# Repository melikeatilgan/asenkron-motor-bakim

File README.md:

# Asenkron motor: arıza analizi, bakım planı ve izleme kartları

15 kW'lık bir pompa motorunun hangi yollardan arızalanabileceğini arıza
ağaçlarıyla çıkardım. Buna göre aylık bakım formunu ve arıza anında kullanılacak
bir cep kartını hazırladım. Analiz, titreşimin ve yatak sıcaklığının iki aylık
kontrol arasında hiç izlenmediğini gösterdi. Bu boşluğu kapatmak için KiCad'de
üç kart tasarladım.

## Proje kısaca

**1. Arıza analizi** ([01-analiz/](01-analiz/)). Motorda ters gidebilecek üç
şeyi ele aldım: aşırı ısınma, aşırı titreşim, aşırı akım. Her birini kök
nedenlerine kadar bir arıza ağacıyla açtım. Python betiği hangi nedenlerin
birlikte arızaya yol açtığını hesaplıyor; aşağıdaki 144 / 21 / 18 sayıları
oradan geliyor. Analizin vardığı sonuç: titreşimi ve yatak sıcaklığını izleyen
otomatik bir koruma yok, bu arızalar ancak ayda bir yapılan kontrolde fark
ediliyor.

**2. Saha dokümanları** ([02-saha-dokumanlari/](02-saha-dokumanlari/)).

- **Aylık bakım formu** (A4, 2 sayfa): teknisyenin her ay doldurduğu 47
  maddelik kontrol listesi. Her madde arıza ağacındaki bir nedene bağlı.
- **Saha kartı** (A6 cep kartı): motor arıza verdiğinde ilk 5 dakikada ne
  yapılacağını anlatıyor. Ön yüzde "ısınıyor / titriyor / akım yüksek"
  adımları ve güvenlik kilitlemesi, arka yüzde bakılacak sınır değerlerin
  tablosu var.

**3. İzleme kartları** ([03-donanim/](03-donanim/)). Aylık kontrolün göremediği
aradaki zamanı bunlar kapatıyor:

- **Sensör başlığı:** motorun gövdesine vidalanıyor. Titreşimi ve iki yatağın
  sıcaklığını (PT100) sürekli ölçüyor, kabloyla ana karta gönderiyor.
- **Ana kart:** elektrik panosunun içinde duruyor. Üç faz akımını ve motor
  sargısındaki PTC sıcaklık sensörünü okuyor, ekran ve LED'lerle durumu
  gösteriyor. Sınır aşılırsa röle kontağını açıp motoru durduruyor. Asıl koruma
  değil; termik rölenin yanında ikinci bir güvenlik katmanı.
- **Telemetri geçidi:** pano dışında, Wi-Fi'li (ESP32). Ölçümleri ana karttan
  okuyup ağa (bilgisayar, telefon) aktarıyor. Yalnızca okuyor; üzerinde motoru
  durduracak bir çıkış yok.

Referans motor: WEG W22 IE3, 15 kW, 4 kutup, 400 V Δ, 160L gövde (ürün kodu
12863072). Değerler üreticinin veri föyünden alındı.

## İzleme kartları

```mermaid
flowchart LR
    MOT(["Motor"])
    SB["Sensör başlığı<br>motorun üstünde"]
    AK["Ana kart<br>pano içinde"]
    KON["Kontaktörün<br>kumanda devresi"]
    TG["Telemetri geçidi<br>pano dışında"]
    AG(["Ağ / SCADA"])
    MOT -- "titreşim, 2 yatak sıcaklığı" --> SB
    MOT -- "3 faz akımı, PTC" --> AK
    SB -- "izole RS-485" --> AK
    AK -- "röle kontağı" --> KON
    AK -- "izole RS-485, Modbus" --> TG
    TG -- "Wi-Fi" --> AG
```

<table>
  <tr>
    <td width="33%" align="center" valign="top">
      
      <br><b>Ana kart</b><br>
      Pano içinde. Faz akımlarını ve PTC'yi ölçer, LCD'de gösterir, sınır aşılırsa motoru durdurur.
      <br>STM32G474 · 190 × 145 mm
    </td>
    <td width="33%" align="center" valign="top">
      
      <br><b>Sensör başlığı</b><br>
      Motorun yatak gövdesine vidalanır. Titreşimi ve iki yatağın sıcaklığını ölçer.
      <br>STM32G071 · 90 × 72 mm
    </td>
    <td width="33%" align="center" valign="top">
      
      <br><b>Telemetri geçidi</b><br>
      Pano dışında. Ölçümleri ana karttan okuyup Wi-Fi ile ağa verir.
      <br>ESP32-S3 · 85 × 70 mm
    </td>
  </tr>
</table>

- **Şebeke gerilimi yalnızca röle kontağında.** O bölge kartın geri kalanından
  frezelenmiş bir yarıkla ayrıldı: 8 mm yüzeysel kaçak, 5,5 mm hava aralığı.
- **PTC girişi takviyeli izole** (ISOW7744). Devre kısa devre, normal, attı ve
  kopuk durumlarını ayırıyor; eşikleri en kötü durum hesabıyla seçtim.
- **Kartlar arası bağlantı izole RS-485.** Motor gövdesiyle pano arasındaki
  toprak farkı ölçüme karışmıyor.
- Üç kart da 4 katman. KiCad ERC ve DRC (şema-kart eşleşmesi dahil) 0.

Her kartın ayrıntısı, şeması ve üretim dosyaları: [03-donanim/](03-donanim/).
Kartlar ana koruma değil; sertifikalı termik röle ve PTC rölesine seri giren bir
erken uyarı katmanı.

## Arıza analizi

1. Üç tepe olay ölçülebilir biçimde tanımlandı: sargı sıcaklığının 155 °C'yi
   aşıp motorun kesilmemesi, yatak gövdesinde titreşimin 4,5 mm/s'yi aşması,
   rejimde akımın anma değerinin %110'unu geçmesi, kalkış akımının izin
   verilenden sık ya da uzun çekilmesi ya da ters akımla frenleme.
2. Her tepe olay VE / VEYA kapılarıyla temel olaylara kadar açıldı. Ağaçlar
   birbirine transferle bağlandı.
3. Minimal kesme kümeleri hesaplandı. Sayılar elle sayılmadı; ağaçlar bir
   betikte tanımlı ve kümeler oradan çıkıyor.
4. Her temel olay için bir kontrol, bir kabul kriteri ve bir periyot yazıldı.
   Betik, form üretecindeki olay kodlarını ağaç tanımlarıyla karşılaştırıyor:
   kontrolü olmayan olay ya da tanımsız kod kalırsa hata veriyor. Kontrolün o
   arızayı gerçekten yakalayıp yakalamadığını denetlemiyor.

| Tepe olay | Minimal kesme kümesi | Tek elemanlı | İki elemanlı | Üç elemanlı |
|---|---|---|---|---|
| T1 Sargı aşırı sıcaklığı kesilmiyor | 144 | 0 | 36 | 108 |
| T2 Titreşim Bölge D | 21 | 20 | 1 | 0 |
| T3 Aşırı akım yüklenmesi | 18 | 18 | 0 | 0 |

T1'in yapısı kısaca şöyle:

```mermaid
flowchart TD
    T1["T1: Sargı sıcaklığı 155 °C'yi aşıyor<br>ve motor kesilmiyor"] --- O1{{VEYA}}
    O1 --- A11["Akımla birlikte gelen<br>ısınma kesilmiyor"]
    O1 --- A12["Akım artmadan gelen<br>ısınma kesilmiyor"]
    A11 --- V1{{VE}}
    V1 --- T3["T3: aşırı akım yüklenmesi<br>(18 olay)"]
    V1 --- O2{{VEYA}}
    O2 --- KON1["Kontaktör yapışmış"]
    O2 --- V2{{VE}}
    V2 --- PTC1["PTC yolu kestirmiyor<br>(2 olay)"]
    V2 --- TR["Termik yol kestirmiyor<br>(3 olay)"]
    A12 --- V3{{VE}}
    V3 --- SOG["Isı dışarı atılamıyor<br>(6 olay)"]
    V3 --- O3{{VEYA}}
    O3 --- KON2["Kontaktör yapışmış"]
    O3 --- PTC2["PTC yolu kestirmiyor<br>(2 olay)"]
```

Buradan üç şey çıkıyor:

- Bu modelde T1'e tek başına giden olay yok. En kısa yollar iki elemanlı:
  herhangi bir ısınma sebebiyle birlikte yapışmış bir kontaktör, ya da bir
  soğutma arızasıyla birlikte çalışmayan PTC yolu.
- Fan ızgarası tıkandığında motorun yükü değişmez, akımı termik röleyi
  açtıracak kadar artmaz. Bu durumda sıcaklığı izleyen tek koruma PTC'dir. PTC
  yolu çalışmıyorsa motoru zamanında kesecek bir şey kalmaz. Form bu yüzden
  PTC, termik röle ve kontaktör kontrolleriyle başlıyor.
- Senaryoda titreşim ve yatak sıcaklığı için otomatik bir izleme yok. İkisi de
  ancak aylık ölçümle fark ediliyor; iki ölçüm arasında gelişen bir yatak
  arızası görülmüyor. İzleme kartları bunun için.

Ayrıntı [kesme-kumeleri.md](01-analiz/kesme-kumeleri.md) içinde.

## Saha dokümanları

Analizden çıkan kontroller iki belgeye dönüştü. İkisi de HTML olarak yazıldı;
yazdırılmış hâlleri PDF:
[aylik-bakim-formu.pdf](02-saha-dokumanlari/aylik-form/aylik-bakim-formu.pdf),
[saha-karti.pdf](02-saha-dokumanlari/saha-karti/saha-karti.pdf).

<table>
  <tr>
    <td width="50%" align="center" valign="top">
      
      <br><b>Aylık bakım formu, 1. sayfa</b><br>
      Teknisyenin her ay doldurduğu kontrol listesi: koruma, elektriksel ve titreşim
      maddeleri. Her satırda kabul kriteri, periyot ve maddenin arıza ağacında hangi
      olayı aradığı yazıyor; teknisyen ölçtüğü değeri ve U (uygun) / X işaretini girer.
    </td>
    <td width="50%" align="center" valign="top">
      
      <br><b>Aylık bakım formu, 2. sayfa</b><br>
      Mekanik, yatak, soğutma ve yük maddeleri. Altta uygun olmayan maddeler için
      açılan iş emirlerinin ve imzaların yazıldığı alan var.
    </td>
  </tr>
  <tr>
    <td width="50%" align="center" valign="top">
      
      <br><b>Saha kartı, ön yüz</b><br>
      A6 cep kartı. Motor arıza verdiğinde ilk 5 dakikada ne yapılacağı: ısınıyor,
      titriyor ya da akımı yüksekse sırayla neye bakılır, motora dokunmadan önce
      enerji nasıl kesilip kilitlenir.
    </td>
    <td width="50%" align="center" valign="top">
      
      <br><b>Saha kartı, arka yüz</b><br>
      Ölçülen değerin karşılaştırılacağı sınırlar: titreşim bölgeleri, spektrumda
      bakılacak frekanslar, motorun ne zaman durdurulacağı, ne zaman iş emri açılacağı.
    </td>
  </tr>
</table>

## Depoda ne var

| Dosya | İçerik |
|---|---|
| [01-analiz/referans-motor.md](01-analiz/referans-motor.md) | Föy değerleri, türetilen değerler, varsayılan işletme senaryosu |
| [01-analiz/T1-asiri-isinma.md](01-analiz/T1-asiri-isinma.md) | T1: sargı aşırı sıcaklığı |
| [01-analiz/T2-titresim.md](01-analiz/T2-titresim.md) | T2: aşırı titreşim |
| [01-analiz/T3-asiri-akim.md](01-analiz/T3-asiri-akim.md) | T3: aşırı akım yüklenmesi |
| [01-analiz/kesme-kumeleri.md](01-analiz/kesme-kumeleri.md) | Minimal kesme kümeleri ve yorumu |
| [01-analiz/kesme_kumeleri.py](01-analiz/kesme_kumeleri.py) | Kümeleri hesaplayan ve formdaki olay kodlarını ağaçlarla karşılaştıran betik |
| [01-analiz/kaynaklar.md](01-analiz/kaynaklar.md) | Kullanılan standartlar, standart dışı değerler, doğrulanmayanlar |
| [02-saha-dokumanlari/aylik-form/](02-saha-dokumanlari/aylik-form/) | 47 maddelik aylık bakım formu (A4, iki sayfa) ve üreteci |
| [02-saha-dokumanlari/saha-karti/](02-saha-dokumanlari/saha-karti/) | Arıza anında bakılacak A6 cep kartı (ön ve arka yüz) |
| [03-donanim/](03-donanim/) | Üç izleme kartı: KiCad projeleri, üretim dosyaları, 3B görüntüler |

## Sınırlar

- Saha ölçümü yok. Analiz belirli bir tesisteki motor için değil, föy ve
  standart değerleriyle bir motor tipi için yapıldı.
- Analiz nitel. Olayların olasılığı ve sonuçlarının şiddeti hesaplanmadı; küme
  sayıları modelin yapısını gösterir, risk büyüklüğü olarak okunmamalı.
- Kısa devre ve toprak arızası koruması kapsam dışı. Termik rölenin motora
  uygunluğu belirli bir rölenin açma eğrisiyle doğrulanmadı; Class 10 başlangıç
  seçimi olarak geçiyor.
- Standart metinlerinin kendisi elimde değildi. Değerler üretici katalogları ve
  uygulama notlarından alındı; hangilerinin standarttan geldiği, hangilerinin bu
  çalışmada seçilen tarama eşiği olduğu [kaynaklar.md](01-analiz/kaynaklar.md)
  içinde ayrı ayrı yazıyor.
- Başka bir motora uygulanırken eşikler o motorun plaka değerleriyle yeniden
  hesaplanmalı.

## Çalıştırmak için

```
python 01-analiz/kesme_kumeleri.py
```

Kümeleri hesaplar ve form üretecindeki olay kodlarını ağaç tanımlarıyla
karşılaştırır.

```
cd 02-saha-dokumanlari/aylik-form
python form-uret.py
```

`aylik-bakim-formu.html` dosyasını yeniden üretir. İkisi de yalnızca Python
standart kütüphanesini kullanır.

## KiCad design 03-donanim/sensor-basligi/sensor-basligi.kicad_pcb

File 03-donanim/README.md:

# İzleme kartları (KiCad)

Arıza analizinde titreşim ve yatak sıcaklığı için otomatik bir koruma olmadığı
çıktı; bunlar ancak aylık kontrolde fark ediliyordu. Motoru sürekli izlemek için
üç kart tasarladım: motorun üstünde ölçen bir sensör başlığı, panoda karar veren
bir ana kart ve ölçümleri ağa aktaran bir telemetri geçidi.

## Nasıl birlikte çalışıyorlar

```mermaid
flowchart LR
    MOT(["Motor"])
    SB["Sensör başlığı<br>motorun üstünde"]
    AK["Ana kart<br>pano içinde"]
    KON["Kontaktörün<br>kumanda devresi"]
    TG["Telemetri geçidi<br>pano dışında"]
    AG(["Ağ / SCADA"])
    MOT -- "titreşim, 2 yatak sıcaklığı" --> SB
    MOT -- "3 faz akımı, PTC" --> AK
    SB -- "izole RS-485" --> AK
    AK -- "röle kontağı" --> KON
    AK -- "izole RS-485, Modbus" --> TG
    TG -- "Wi-Fi" --> AG
```

Ana kart diğer ikisi olmadan da çalışır: akımı ve PTC'yi kendisi ölçer, röleyi
kendisi açar. Sensör başlığı titreşim ve yatak sıcaklığını ekler, geçit yalnızca
izleme içindir.

**Ana koruma değil.** Kartın röle kontağı, sertifikalı termik röle ve PTC
rölesiyle birlikte kumanda devresine seri girer. Kart arızalansa da onlar
görevini yapar. Röle normalde çekili; kartın beslemesi kesilirse kontak açılır
ve motor durur.

Aşağıda her kartın tasarlandığı işi yazdım; bu işleri yürütecek firmware bu
depoda yok.

## Ana kart

Elektrik panosunun içine takılır, 24 V DC ile beslenir.

- Üç faz akımını akım trafolarıyla ölçer.
- Motor sargısındaki PTC sıcaklık sensörlerini izole bir girişle okur; kısa
  devre, normal, attı ve kopuk durumlarını ayırır.
- Sensör başlığından titreşim ve yatak sıcaklıklarını alır.
- Bir sınır aşılırsa röle kontağını açar. Kontak kontaktörün kumanda devresine
  seri bağlı; açılınca kontaktör bobini enerjisiz kalır ve kontaktör motorun
  beslemesini keser.
- Durumu LCD'de ve titreşim bölgesini gösteren LED'lerde (yeşil A/B, sarı C,
  kırmızı D) gösterir; üç buton (<, >, OK) var.
- Ölçümleri izole RS-485 üzerinden Modbus ile geçide verir.

**Üzerinde:** STM32G474 · ISOW7744 (PTC izolatörü) · 2 × ADM2582E (izole
RS-485) · LM5164 (24 V → 3,3 V) · LM339B · Finder 34.51 röle · EA DOGM128 LCD.
190 × 145 mm, 4 katman.

**Dosyalar:** [KiCad projesi](ana-kart/) ·
[şematik (PDF)](uretim/ana-kart/motor-izleme-karti-sematik.pdf) ·
[kart katmanları (PDF)](uretim/ana-kart/motor-izleme-karti-kart.pdf) ·
[Gerber](uretim/ana-kart/motor-izleme-karti-gerber.zip) ·
[malzeme listesi](uretim/ana-kart/motor-izleme-karti-bom.csv) ·
[STEP](uretim/ana-kart/motor-izleme-karti.step)

## Sensör başlığı

Motorun yatak gövdesine vidalanır. Besleme ve haberleşme aynı kablodan gelir
(24 V, 0 V, RS-485 A/B, izole toprak).

- Titreşimi IIS3DWB ivmeölçerle ölçer; geniş bantlı olduğu için spektruma
  bakılabilir (dengesizlik, kaçıklık, yatak frekansları).
- Ön ve arka yatağın sıcaklığını iki PT100 ile ölçer; 4 telli bağlantı
  sayesinde kablo direnci ölçüme girmez.
- Ölçümleri izole RS-485 ile ana karta gönderir.

**Üzerinde:** STM32G071 · IIS3DWB · 2 × MAX31865 · ADM2582E · LM5164.
90 × 72 mm, 4 katman.

**Dosyalar:** [KiCad projesi](sensor-basligi/) ·
[şematik (PDF)](uretim/sensor-basligi/sensor-basligi-sematik.pdf) ·
[kart katmanları (PDF)](uretim/sensor-basligi/sensor-basligi-kart.pdf) ·
[Gerber](uretim/sensor-basligi/sensor-basligi-gerber.zip) ·
[malzeme listesi](uretim/sensor-basligi/sensor-basligi-bom.csv) ·
[STEP](uretim/sensor-basligi/sensor-basligi.step)

## Telemetri geçidi

Pano dışına konur; metal pano radyo sinyalini zayıflattığı için Wi-Fi modülünün
anteni IPEX konnektörle dışarı alınır.

- Ana karttaki ölçümleri izole RS-485 üzerinden Modbus RTU ile okur.
- Ölçümleri Wi-Fi üzerinden MQTT ile ağa aktarmak için; böylece motor
  bilgisayardan ya da telefondan izlenebilir.
- Yalnızca okumak için düşünüldü. Kartta röle ya da kumanda çıkışı yok; motoru
  durdurabilen tek kart ana kart.

**Üzerinde:** ESP32-S3-WROOM-1U · ADM2582E · LM5164. 85 × 70 mm, 4 katman.

**Dosyalar:** [KiCad projesi](telemetri-gecidi/) ·
[şematik (PDF)](uretim/telemetri-gecidi/telemetri-gecidi-sematik.pdf) ·
[kart katmanları (PDF)](uretim/telemetri-gecidi/telemetri-gecidi-kart.pdf) ·
[Gerber](uretim/telemetri-gecidi/telemetri-gecidi-gerber.zip) ·
[malzeme listesi](uretim/telemetri-gecidi/telemetri-gecidi-bom.csv) ·
[STEP](uretim/telemetri-gecidi/telemetri-gecidi.step)

## Tasarım kararları

**Şebeke yalnızca röle kontağında.** Kart 24 V DC ile beslenir. Kontağın
bulunduğu bölgeyi kartın geri kalanından frezelenmiş bir yarıkla ayırdım.
Aradaki mesafe takviyeli yalıtıma göre: 5,5 mm hava, 8 mm yüzeysel kaçak
(IEC 60664-1, 230/400 V, aşırı gerilim kategorisi III).

**PTC girişi takviyeli izole.** PTC sargının içine gömülü olduğu için sargıyla
PTC arasındaki yalıtım delinirse kablolar şebeke potansiyeline çıkabilir. Giriş
ISOW7744 ile ayrıldı, kart üzerinde 8 mm boşluk var. Eşikleri direnç toleransı,
karşılaştırıcının ofseti ile giriş akımı ve besleme değişimi birlikte en kötü
duruma çekilerek hesapladım; attı eşiği IEC 60947-8'in 1650–4000 Ω penceresinde
kalıyor.

**Giriş koruması.** Besleme girişinde sırasıyla sigorta, çift yönlü TVS
(darbede en çok 53,3 V), ters kutup için seri Schottky, ortak mod bobini ve
100 V'luk bir buck dönüştürücü (LM5164) var.

**İzole RS-485** (ADM2582E). Sensör başlığının toprağı motor gövdesinde, Modbus
hattınınki panoda; aradaki potansiyel farkı ölçüme karışmasın diye.

## Kontroller

| | Ana kart | Sensör başlığı | Telemetri geçidi |
|---|---|---|---|
| ERC | 0 | 0 | 0 |
| DRC, hata ve uyarı | 0 | 0 | 0 |
| Bağlanmamış nokta | 0 | 0 | 0 |
| İzole bölge ile geri kalan bakır arası | PTC 8,04 mm, RS-485 3,05 mm | 2,05 mm | 2,03 mm |

ERC ve DRC KiCad 10'un kendi denetimleri; DRC şema-kart eşleşmesi dahil. Son
satırdaki mesafeler bakırdan bakıra (iz, pad, via ve dolgu), dört katmanın her
birinde ölçülen en küçük değer.

ERC ve DRC sıfır olsa da devre yanlış olabilir: ters takılmış bir diyot ya da
yanlış sargıdan bağlanmış bir bobin elektriksel olarak geçerli bir bağlantıdır.
Bu yüzden netlisti bacak adlarına göre ayrıca kontrol ettim: diyotların yönü,
izolatör bacaklarının hangi tarafa bağlı olduğu, sensör uyarım bağlantıları
gibi. Bu kontrolün kaydı depoda yok. Yerleşimde dekuplaj kondansatörlerinin
entegre bacağına uzaklığına (≤ 3 mm), kristalin mikrodenetleyiciye uzaklığına ve
buck dönüştürücünün anahtarlama düğümüne yönlendirmeden önce baktım.

Kartları otomatik yönlendiriciyle (Freerouting) yönlendirdim, şebeke izlerini
elle çizdim. Şematiğin her sayfasında o sayfanın tasarım notları ve hesapları
yazılı. Bileşen referansları montaj katmanında (kart PDF'i); ipek baskıda
yalnızca bağlantı ve blok adlarını bıraktım.

## Klasörler

| Klasör | İçerik |
|---|---|
| [ana-kart/](ana-kart/), [sensor-basligi/](sensor-basligi/), [telemetri-gecidi/](telemetri-gecidi/) | KiCad 10 projeleri (şematik, kart, kurallar) |
| [uretim/](uretim/) | Her kart için Gerber + delik dosyası (zip), şematik ve kart PDF'i, malzeme listesi, yerleştirme dosyası, STEP |
| [3d/](3d/) | KiCad kütüphanesinde olmayan LCD ve ESP32 modülünün 3B modelleri |
| [ayak/](ayak/) | Standart kütüphaneden türettiğim iki ayak izi: iç aralığı 8,1 mm'ye daraltılmış SOIC-20W (PTC izolatörü) ve ipek baskısı montaj katmanına alınmış röle |
| [gorseller/](gorseller/) | 3B görüntüler |

## Açık noktalar

- Yazılım (firmware) bu depoda yok; buradaki iş donanım ve eşik hesapları.
- RS-485 hattındaki SM712 koruması 1 A darbede +19 / −11 V'a kırpar,
  transceiver'ın hat bacakları −9 / +14 V'a dayanır. Hat koruması, hedeflenen
  darbe sınıfı belli olunca yeniden boyutlandırılmalı.
- Akım trafosunun sipariş kodu seçilmedi; ölçeklendirme 100 A : 50 mA (2000:1)
  varsayımıyla yapıldı.
- İç katmanlar ağırlıklı GND ama kesintisiz bir referans düzlemi değil: birinci
  iç katmandan sinyal izi de geçiyor (ana kartta 1,34 m, sensör başlığında
  0,66 m, geçitte 0,24 m). Bu katmanın GND ile dolu kısmı sırasıyla kart
  alanının %64, %76 ve %79'u.
- Röle kontağındaki RC söndürücü takılmaz olarak işaretli: açık kontak üzerinden
  sızan ~7 mA küçük bir kontaktörü bıraktırmayabilir. Yük bilinince takılır.
- Motorun PTC zinciri hem sertifikalı PTC rölesine hem bu karta paralel
  bağlanamaz. Motorda tek zincir varsa röleye gider; bu giriş ikinci zincir içindir.

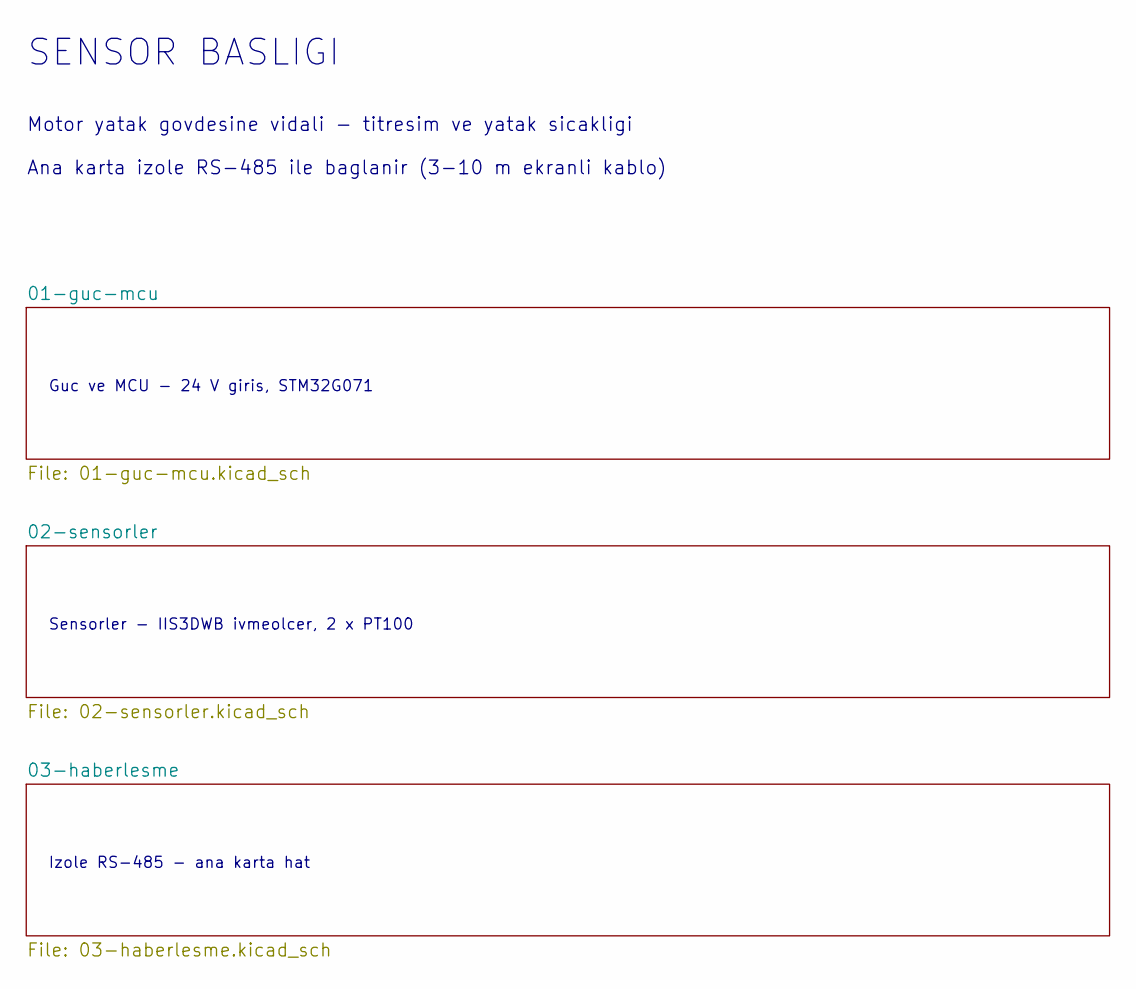
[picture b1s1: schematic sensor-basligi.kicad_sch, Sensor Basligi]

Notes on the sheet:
SENSOR BASLIGI
Motor yatak govdesine vidali - titresim ve yatak sicakligi
Guc ve MCU - 24 V giris, STM32G071
Sensorler - IIS3DWB ivmeolcer, 2 x PT100
Izole RS-485 - ana karta hat
Ana karta izole RS-485 ile baglanir (3-10 m ekranli kablo)

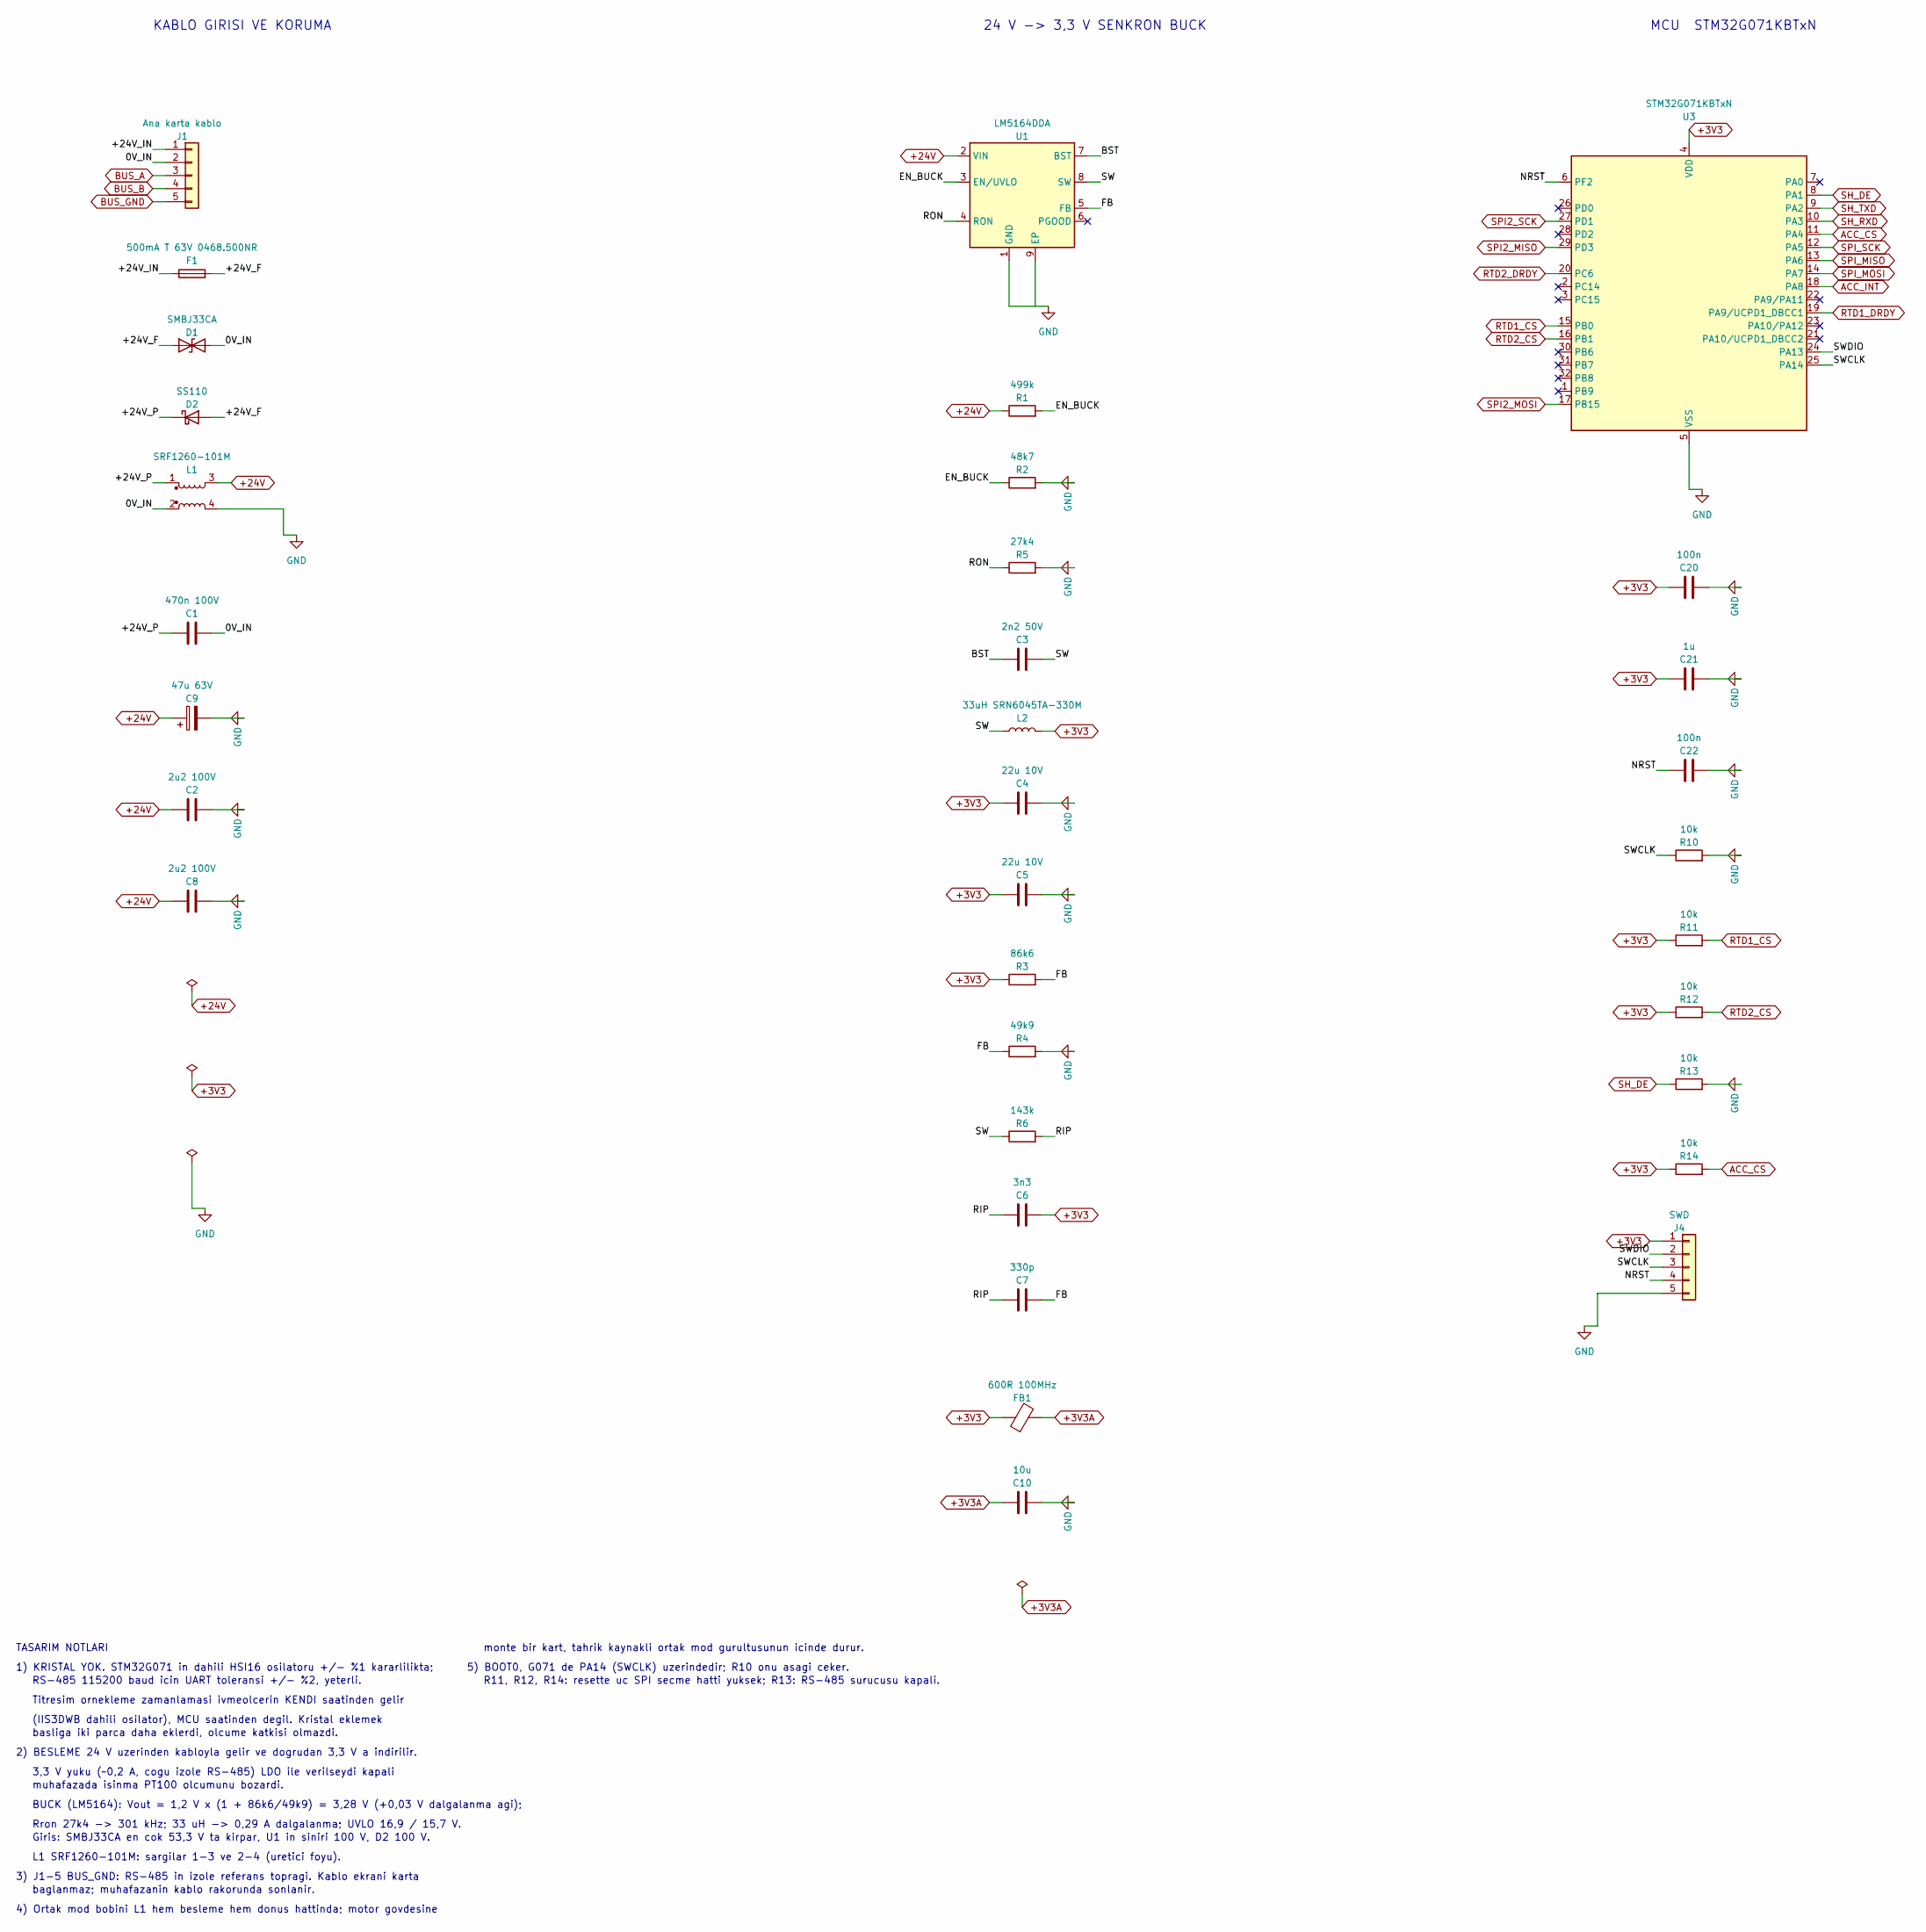
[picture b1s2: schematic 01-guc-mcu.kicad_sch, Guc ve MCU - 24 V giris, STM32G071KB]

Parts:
C1: 470n 100V; C_1206_3216Metric
C2, C8: 2u2 100V; C_1210_3225Metric
C3: 2n2 50V; C_0805_2012Metric
C4, C5: 22u 10V; C_1206_3216Metric
C6: 3n3; C_0805_2012Metric
C7: 330p; C_0805_2012Metric
C9: 47u 63V; CP_Radial_D8.0mm_P3.50mm
C10: 10u; C_1206_3216Metric
C20, C22: 100n; C_0805_2012Metric
C21: 1u; C_0805_2012Metric
D1: SMBJ33CA; D_SMB
D2: SS110; D_SMA
F1: 500mA T 63V 0468.500NR; Fuse_1206_3216Metric
FB1: 600R 100MHz; L_0805_2012Metric
J1: Ana karta kablo; TerminalBlock_Phoenix_MKDS-1,5-5_1x05_P5.00mm_Horizontal
J4: SWD; PinHeader_1x05_P2.54mm_Vertical
L1: SRF1260-101M; L_CommonModeChoke_Bourns_SRF1260
L2: 33uH SRN6045TA-330M; L_Bourns_SRN6045TA
R1: 499k; R_0805_2012Metric
R2: 48k7; R_0805_2012Metric
R3: 86k6; R_0805_2012Metric
R4: 49k9; R_0805_2012Metric
R5: 27k4; R_0805_2012Metric
R6: 143k; R_0805_2012Metric
R10, R11, R12, R13, R14: 10k; R_0805_2012Metric
U1: LM5164DDA; HSOP-8-1EP_3.9x4.9mm_P1.27mm_EP2.41x3.1mm_ThermalVias
U3: STM32G071KBTxN; LQFP-32_7x7mm_P0.8mm

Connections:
+3V3: C4.1, C5.1, C6.2, C20.1, C21.1, FB1.1, J4.1, L2.2, R3.1, R11.1, R12.1, R14.1, U3.4 (VDD); also elsewhere on the board
+3V3A: C10.1, FB1.2; also elsewhere on the board
+24V: C2.1, C8.1, C9.1, L1.3, R1.1, U1.2 (VIN)
/01-guc-mcu/0V_IN: C1.2, D1.2 (A2), J1.2, L1.2
/01-guc-mcu/+24V_F: D1.1 (A1), D2.2 (A), F1.2
/01-guc-mcu/+24V_IN: F1.1, J1.1
/01-guc-mcu/+24V_P: C1.1, D2.1 (K), L1.1
/01-guc-mcu/BST: C3.1, U1.7 (BST)
/01-guc-mcu/EN_BUCK: R1.2, R2.1, U1.3 (EN/UVLO)
/01-guc-mcu/FB: C7.2, R3.2, R4.1, U1.5 (FB)
/01-guc-mcu/NRST: C22.1, J4.4, U3.6 (PF2)
/01-guc-mcu/RIP: C6.1, C7.1, R6.2
/01-guc-mcu/RON: R5.1, U1.4 (RON)
/01-guc-mcu/SW: C3.2, L2.1, R6.1, U1.8 (SW)
/01-guc-mcu/SWCLK: J4.3, R10.1, U3.25 (PA14)
/01-guc-mcu/SWDIO: J4.2, U3.24 (PA13)
ACC_CS: R14.2, U3.11 (PA4); also elsewhere on the board
ACC_INT: U3.18 (PA8); also elsewhere on the board
BUS_A: J1.3; also elsewhere on the board
BUS_B: J1.4; also elsewhere on the board
BUS_GND: J1.5; also elsewhere on the board
GND: C2.2, C4.2, C5.2, C8.2, C9.2, C10.2, C20.2, C21.2, C22.2, J4.5, L1.4, R2.2, R4.2, R5.2, R10.2, R13.2, U1.1 (GND), U1.9 (EP), U3.5 (VSS); also elsewhere on the board
RTD1_CS: R11.2, U3.15 (PB0); also elsewhere on the board
RTD1_DRDY: U3.19 (PA9/UCPD1_DBCC1); also elsewhere on the board
RTD2_CS: R12.2, U3.16 (PB1); also elsewhere on the board
RTD2_DRDY: U3.20 (PC6); also elsewhere on the board
SH_DE: R13.1, U3.8 (PA1); also elsewhere on the board
SH_RXD: U3.10 (PA3); also elsewhere on the board
SH_TXD: U3.9 (PA2); also elsewhere on the board
SPI2_MISO: U3.29 (PD3); also elsewhere on the board
SPI2_MOSI: U3.17 (PB15); also elsewhere on the board
SPI2_SCK: U3.27 (PD1); also elsewhere on the board
SPI_MISO: U3.13 (PA6); also elsewhere on the board
SPI_MOSI: U3.14 (PA7); also elsewhere on the board
SPI_SCK: U3.12 (PA5); also elsewhere on the board

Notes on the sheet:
1) KRISTAL YOK. STM32G071 in dahili HSI16 osilatoru +/- %1 kararlilikta;
4) Ortak mod bobini L1 hem besleme hem donus hattinda; motor govdesine
MCU STM32G071KBTxN
Rron 27k4 -> 301 kHz; 33 uH -> 0,29 A dalgalanma; UVLO 16,9 / 15,7 V.
3,3 V yuku (~0,2 A, cogu izole RS-485) LDO ile verilseydi kapali
L1 SRF1260-101M: sargilar 1-3 ve 2-4 (uretici foyu).
KABLO GIRISI VE KORUMA
TASARIM NOTLARI
monte bir kart, tahrik kaynakli ortak mod gurultusunun icinde durur.
(IIS3DWB dahili osilator), MCU saatinden degil. Kristal eklemek
RS-485 115200 baud icin UART toleransi +/- %2, yeterli.
24 V -> 3,3 V SENKRON BUCK
R11, R12, R14: resette uc SPI secme hatti yuksek; R13: RS-485 surucusu kapali.
basliga iki parca daha eklerdi, olcume katkisi olmazdi.
3) J1-5 BUS_GND: RS-485 in izole referans topragi. Kablo ekrani karta
Giris: SMBJ33CA en cok 53,3 V ta kirpar, U1 in siniri 100 V, D2 100 V.
baglanmaz; muhafazanin kablo rakorunda sonlanir.
2) BESLEME 24 V uzerinden kabloyla gelir ve dogrudan 3,3 V a indirilir.
muhafazada isinma PT100 olcumunu bozardi.
5) BOOT0, G071 de PA14 (SWCLK) uzerindedir; R10 onu asagi ceker.
Titresim ornekleme zamanlamasi ivmeolcerin KENDI saatinden gelir
BUCK (LM5164): Vout = 1,2 V x (1 + 86k6/49k9) = 3,28 V (+0,03 V dalgalanma agi);

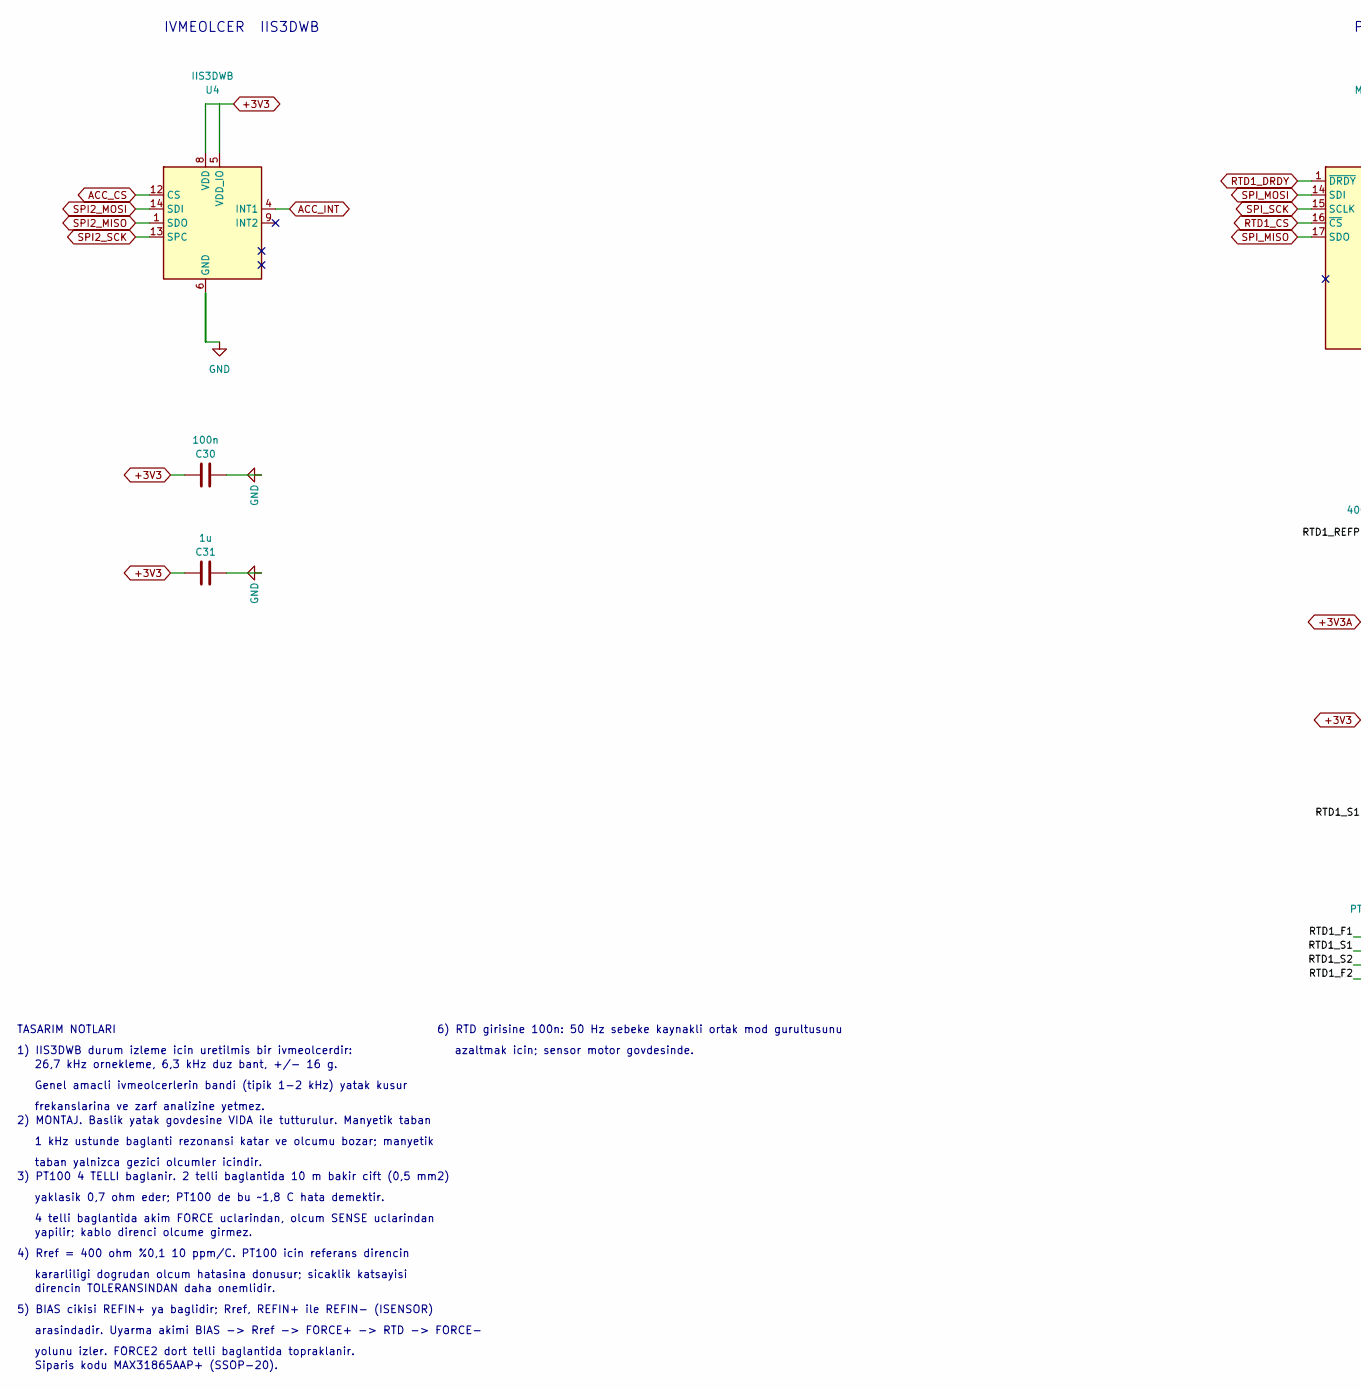
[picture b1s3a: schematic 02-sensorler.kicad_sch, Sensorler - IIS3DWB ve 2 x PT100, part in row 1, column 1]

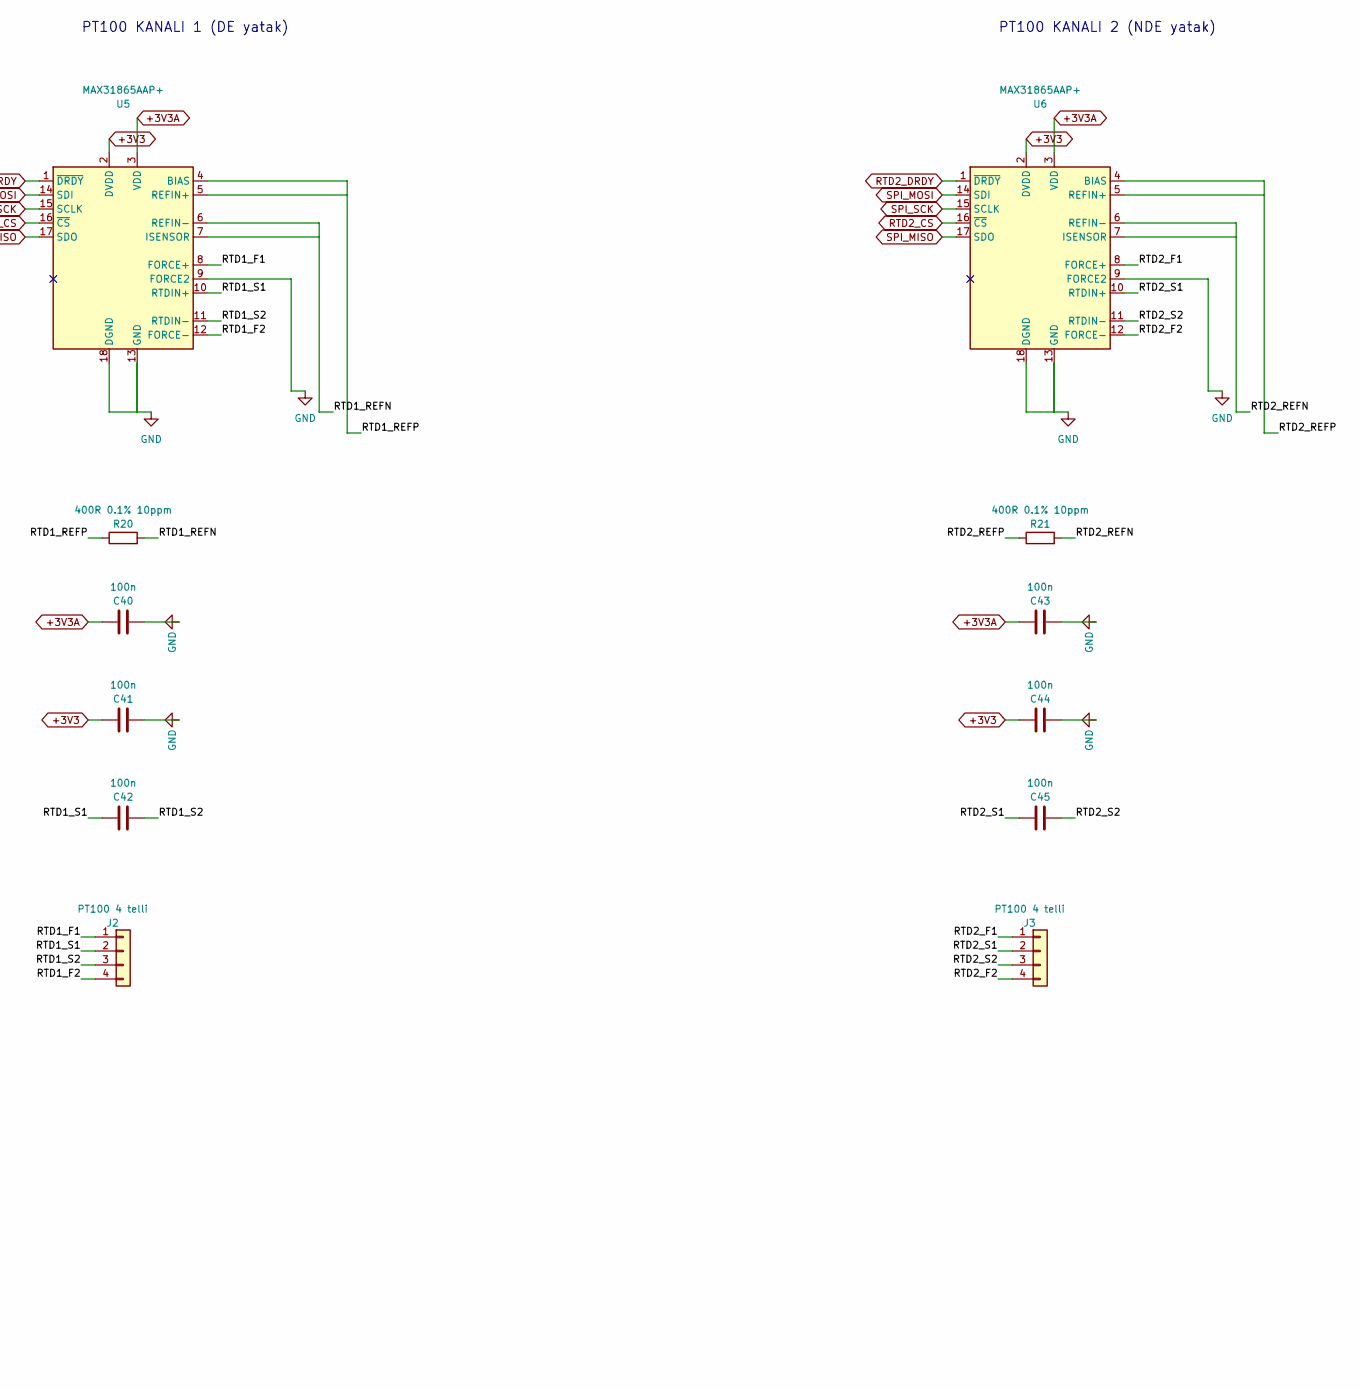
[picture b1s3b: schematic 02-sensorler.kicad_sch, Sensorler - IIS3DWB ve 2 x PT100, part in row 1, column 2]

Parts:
C30, C40, C41, C42, C43, C44, C45: 100n; C_0805_2012Metric
C31: 1u; C_0805_2012Metric
J2, J3: PT100 4 telli; TerminalBlock_Phoenix_MPT-0,5-4-2.54_1x04_P2.54mm_Horizontal
R20, R21: 400R 0.1% 10ppm; R_0805_2012Metric
U4: IIS3DWB; LGA-14_3x2.5mm_P0.5mm_LayoutBorder3x4y
U5, U6: MAX31865AAP+; SSOP-20_5.3x7.2mm_P0.65mm

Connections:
+3V3: C30.1, C31.1, C41.1, C44.1, U4.5 (VDD_IO), U4.8 (VDD), U5.2 (DVDD), U6.2 (DVDD); also elsewhere on the board
+3V3A: C40.1, C43.1, U5.3 (VDD), U6.3 (VDD); also elsewhere on the board
/02-sensorler/RTD1_F1: J2.1, U5.8 (FORCE+)
/02-sensorler/RTD1_F2: J2.4, U5.12 (FORCE-)
/02-sensorler/RTD1_REFN: R20.2, U5.6 (REFIN-), U5.7 (ISENSOR)
/02-sensorler/RTD1_REFP: R20.1, U5.4 (BIAS), U5.5 (REFIN+)
/02-sensorler/RTD1_S1: C42.1, J2.2, U5.10 (RTDIN+)
/02-sensorler/RTD1_S2: C42.2, J2.3, U5.11 (RTDIN-)
/02-sensorler/RTD2_F1: J3.1, U6.8 (FORCE+)
/02-sensorler/RTD2_F2: J3.4, U6.12 (FORCE-)
/02-sensorler/RTD2_REFN: R21.2, U6.6 (REFIN-), U6.7 (ISENSOR)
/02-sensorler/RTD2_REFP: R21.1, U6.4 (BIAS), U6.5 (REFIN+)
/02-sensorler/RTD2_S1: C45.1, J3.2, U6.10 (RTDIN+)
/02-sensorler/RTD2_S2: C45.2, J3.3, U6.11 (RTDIN-)
ACC_CS: U4.12 (CS); also elsewhere on the board
ACC_INT: U4.4 (INT1); also elsewhere on the board
GND: C30.2, C31.2, C40.2, C41.2, C43.2, C44.2, U4.2 (GND), U4.3 (GND), U4.6 (GND), U4.7 (GND), U5.9 (FORCE2), U5.13 (GND), U5.18 (DGND), U5.19 (GND), U6.9 (FORCE2), U6.13 (GND), U6.18 (DGND), U6.19 (GND); also elsewhere on the board
RTD1_CS: U5.16 (~CS); also elsewhere on the board
RTD1_DRDY: U5.1 (~DRDY); also elsewhere on the board
RTD2_CS: U6.16 (~CS); also elsewhere on the board
RTD2_DRDY: U6.1 (~DRDY); also elsewhere on the board
SPI2_MISO: U4.1 (SDO); also elsewhere on the board
SPI2_MOSI: U4.14 (SDI); also elsewhere on the board
SPI2_SCK: U4.13 (SPC); also elsewhere on the board
SPI_MISO: U5.17 (SDO), U6.17 (SDO); also elsewhere on the board
SPI_MOSI: U5.14 (SDI), U6.14 (SDI); also elsewhere on the board
SPI_SCK: U5.15 (SCLK), U6.15 (SCLK); also elsewhere on the board

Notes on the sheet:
2) MONTAJ. Baslik yatak govdesine VIDA ile tutturulur. Manyetik taban
yolunu izler. FORCE2 dort telli baglantida topraklanir.
4) Rref = 400 ohm %0,1 10 ppm/C. PT100 icin referans direncin
frekanslarina ve zarf analizine yetmez.
4 telli baglantida akim FORCE uclarindan, olcum SENSE uclarindan
IVMEOLCER IIS3DWB
PT100 KANALI 1 (DE yatak)
3) PT100 4 TELLI baglanir. 2 telli baglantida 10 m bakir cift (0,5 mm2)
Siparis kodu MAX31865AAP+ (SSOP-20).
5) BIAS cikisi REFIN+ ya baglidir; Rref, REFIN+ ile REFIN- (ISENSOR)
6) RTD girisine 100n: 50 Hz sebeke kaynakli ortak mod gurultusunu
direncin TOLERANSINDAN daha onemlidir.
1) IIS3DWB durum izleme icin uretilmis bir ivmeolcerdir:
1 kHz ustunde baglanti rezonansi katar ve olcumu bozar; manyetik
Genel amacli ivmeolcerlerin bandi (tipik 1-2 kHz) yatak kusur
kararliligi dogrudan olcum hatasina donusur; sicaklik katsayisi
taban yalnizca gezici olcumler icindir.
PT100 KANALI 2 (NDE yatak)
azaltmak icin; sensor motor govdesinde.
yapilir; kablo direnci olcume girmez.
yaklasik 0,7 ohm eder; PT100 de bu ~1,8 C hata demektir.
arasindadir. Uyarma akimi BIAS -> Rref -> FORCE+ -> RTD -> FORCE-
TASARIM NOTLARI
26,7 kHz ornekleme, 6,3 kHz duz bant, +/- 16 g.

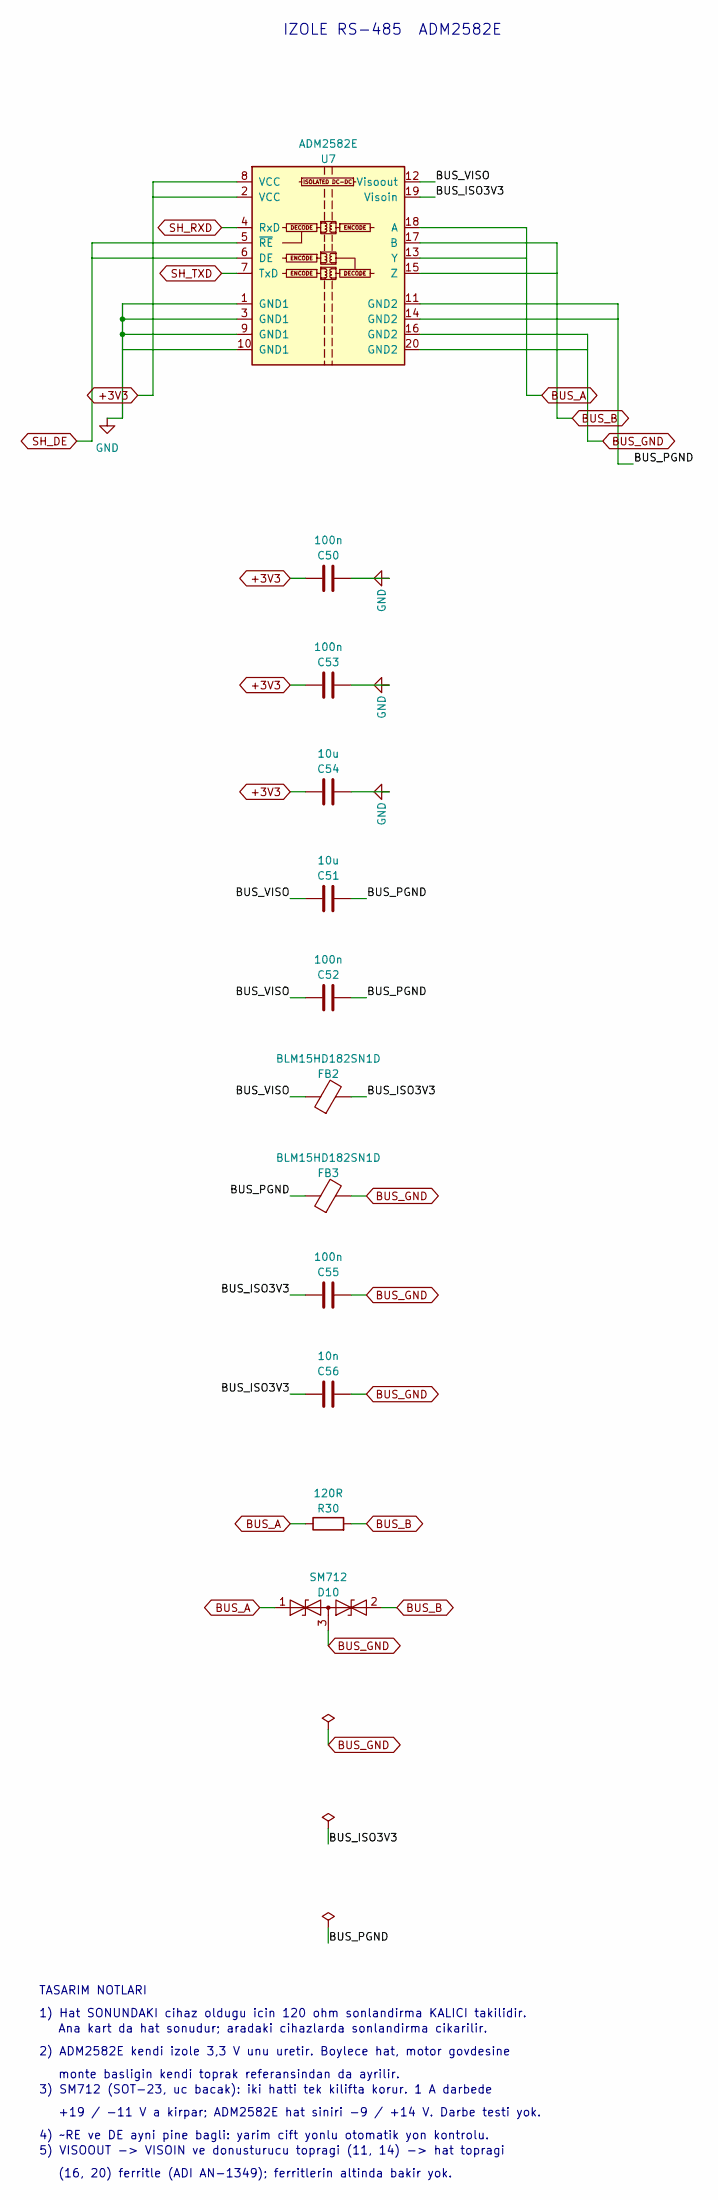
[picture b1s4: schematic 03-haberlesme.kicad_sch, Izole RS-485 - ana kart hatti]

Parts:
C50, C52, C53, C55: 100n; C_0805_2012Metric
C51, C54: 10u; C_1206_3216Metric
C56: 10n; C_0805_2012Metric
D10: SM712; SOT-23
FB2, FB3: BLM15HD182SN1D; L_0402_1005Metric
R30: 120R; R_0805_2012Metric
U7: ADM2582E; SOIC-20W_7.5x12.8mm_P1.27mm

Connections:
+3V3: C50.1, C53.1, C54.1, U7.2 (VCC), U7.8 (VCC); also elsewhere on the board
/03-haberlesme/BUS_ISO3V3: C55.1, C56.1, FB2.2, U7.19 (Visoin)
/03-haberlesme/BUS_PGND: C51.2, C52.2, FB3.1, U7.11 (GND2), U7.14 (GND2)
/03-haberlesme/BUS_VISO: C51.1, C52.1, FB2.1, U7.12 (Visoout)
BUS_A: D10.1 (A1), R30.1, U7.13 (Y), U7.18 (A); also elsewhere on the board
BUS_B: D10.2 (A2), R30.2, U7.15 (Z), U7.17 (B); also elsewhere on the board
BUS_GND: C55.2, C56.2, D10.3 (common), FB3.2, U7.16 (GND2), U7.20 (GND2); also elsewhere on the board
GND: C50.2, C53.2, C54.2, U7.1 (GND1), U7.3 (GND1), U7.9 (GND1), U7.10 (GND1); also elsewhere on the board
SH_DE: U7.5 (~RE), U7.6 (DE); also elsewhere on the board
SH_RXD: U7.4 (RxD); also elsewhere on the board
SH_TXD: U7.7 (TxD); also elsewhere on the board

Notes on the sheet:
TASARIM NOTLARI
IZOLE RS-485 ADM2582E
(16, 20) ferritle (ADI AN-1349); ferritlerin altinda bakir yok.
3) SM712 (SOT-23, uc bacak): iki hatti tek kilifta korur. 1 A darbede
4) ~RE ve DE ayni pine bagli: yarim cift yonlu otomatik yon kontrolu.
2) ADM2582E kendi izole 3,3 V unu uretir. Boylece hat, motor govdesine
+19 / -11 V a kirpar; ADM2582E hat siniri -9 / +14 V. Darbe testi yok.
1) Hat SONUNDAKI cihaz oldugu icin 120 ohm sonlandirma KALICI takilidir.
monte basligin kendi toprak referansindan da ayrilir.
Ana kart da hat sonudur; aradaki cihazlarda sonlandirma cikarilir.
5) VISOOUT -> VISOIN ve donusturucu topragi (11, 14) -> hat topragi
